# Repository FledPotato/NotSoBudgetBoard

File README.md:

# NotSoBudgetBoard
First keyboard design, which definitely won't save myself or anyone else money.

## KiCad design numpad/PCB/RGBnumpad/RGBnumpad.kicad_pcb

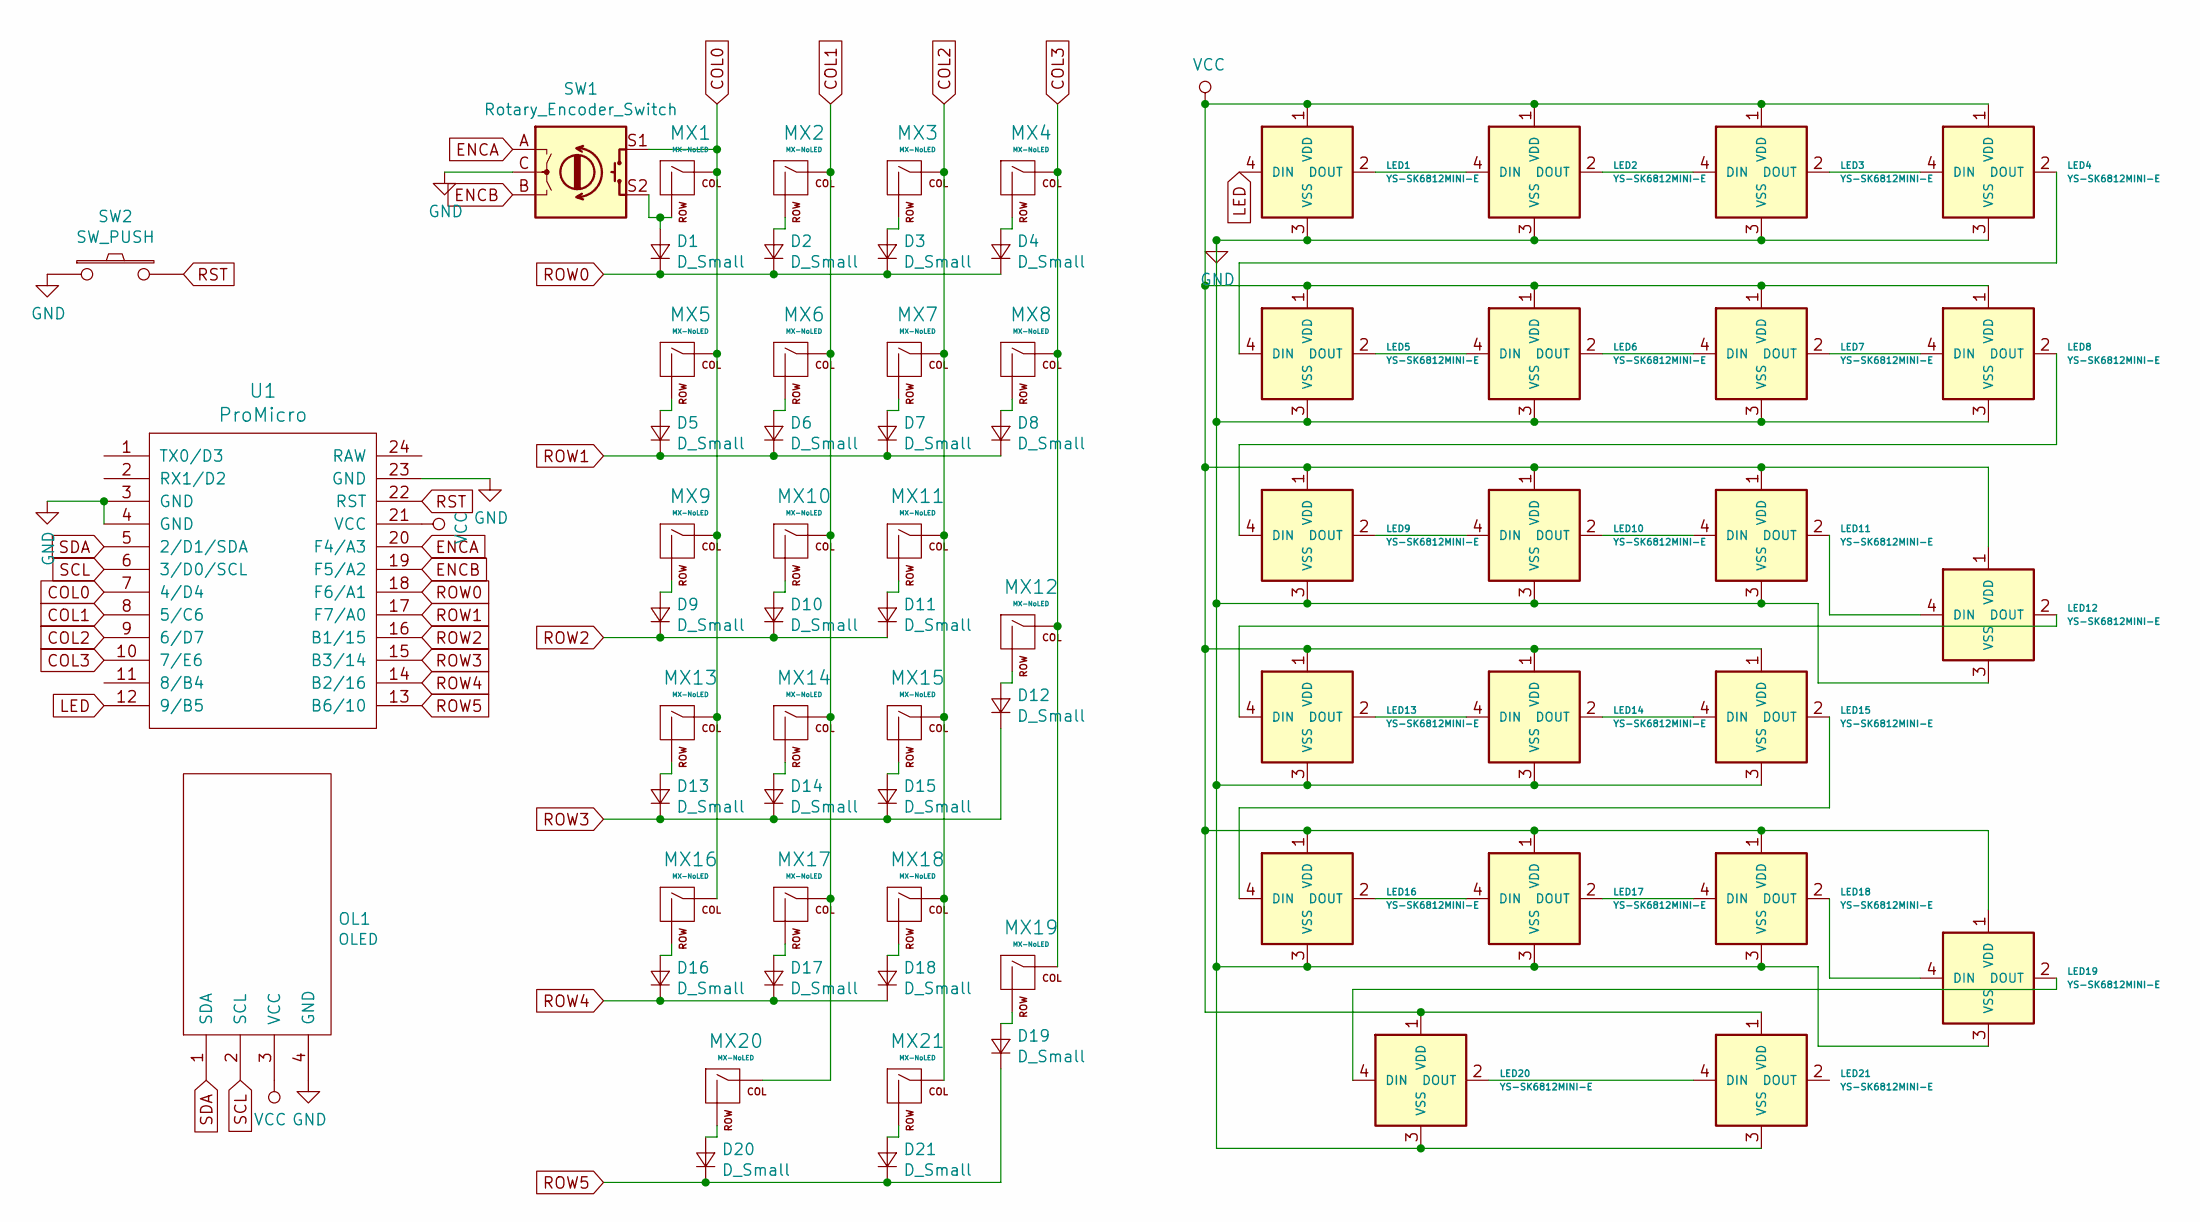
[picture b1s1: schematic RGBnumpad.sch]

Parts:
D1, D2, D3, D4, D5, D6, D7, D8, D9, D10, D11, D12, D13, D14, D15, D16, D17, D18, D19, D20, D21: D_Small; D_DO-35_SOD27_P7.62mm_Horizontal
LED1, LED2, LED3, LED4, LED5, LED6, LED7, LED8, LED9, LED10, LED11, LED12, LED13, LED14, LED15, LED16, LED17, LED18, LED19, LED20, LED21: YS-SK6812MINI-E
MX1, MX2, MX3, MX4, MX5, MX6, MX7, MX8, MX9, MX10, MX11, MX13, MX14, MX15, MX16, MX17, MX18, MX21: MX-NoLED; MXOnly-1U-NoLED
MX12, MX19, MX20: MX-NoLED; MXOnly-2U-ReversedStabilizers-NoLED
OL1: OLED; OLED_v2
SW1: Rotary_Encoder_Switch; RotaryEncoder_Alps_EC11E-Switch_Vertical_H20mm
SW2: SW_PUSH; ResetSW
U1: ProMicro; ProMicro_v3

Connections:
COL0: MX1.1 (COL), MX5.1 (COL), MX9.1 (COL), MX13.1 (COL), MX16.1 (COL), SW1.S1, U1.7 (4/D4)
COL1: MX2.1 (COL), MX6.1 (COL), MX10.1 (COL), MX14.1 (COL), MX17.1 (COL), MX20.1 (COL), U1.8 (5/C6)
COL2: MX3.1 (COL), MX7.1 (COL), MX11.1 (COL), MX15.1 (COL), MX18.1 (COL), MX21.1 (COL), U1.9 (6/D7)
COL3: MX4.1 (COL), MX8.1 (COL), MX12.1 (COL), MX19.1 (COL), U1.10 (7/E6)
ENCA: SW1.A, U1.20 (F4/A3)
ENCB: SW1.B, U1.19 (F5/A2)
GND: LED1.3 (VSS), LED2.3 (VSS), LED3.3 (VSS), LED4.3 (VSS), LED5.3 (VSS), LED6.3 (VSS), LED7.3 (VSS), LED8.3 (VSS), LED9.3 (VSS), LED10.3 (VSS), LED11.3 (VSS), LED12.3 (VSS), LED13.3 (VSS), LED14.3 (VSS), LED15.3 (VSS), LED16.3 (VSS), LED17.3 (VSS), LED18.3 (VSS), LED19.3 (VSS), LED20.3 (VSS), LED21.3 (VSS), OL1.4 (GND), SW1.C, SW2.1, U1.3 (GND), U1.4 (GND), U1.23 (GND)
LED: LED1.4 (DIN), U1.12 (9/B5)
unnamed: D1.2 (A), MX1.2 (ROW), SW1.S2
unnamed: D2.2 (A), MX2.2 (ROW)
unnamed: D3.2 (A), MX3.2 (ROW)
unnamed: D4.2 (A), MX4.2 (ROW)
unnamed: D5.2 (A), MX5.2 (ROW)
unnamed: D6.2 (A), MX6.2 (ROW)
unnamed: D7.2 (A), MX7.2 (ROW)
unnamed: D8.2 (A), MX8.2 (ROW)
unnamed: D9.2 (A), MX9.2 (ROW)
unnamed: D10.2 (A), MX10.2 (ROW)
unnamed: D11.2 (A), MX11.2 (ROW)
unnamed: D12.2 (A), MX12.2 (ROW)
unnamed: D13.2 (A), MX13.2 (ROW)
unnamed: D14.2 (A), MX14.2 (ROW)
unnamed: D15.2 (A), MX15.2 (ROW)
unnamed: D16.2 (A), MX16.2 (ROW)
unnamed: D17.2 (A), MX17.2 (ROW)
unnamed: D18.2 (A), MX18.2 (ROW)
unnamed: D19.2 (A), MX19.2 (ROW)
unnamed: D20.2 (A), MX20.2 (ROW)
unnamed: D21.2 (A), MX21.2 (ROW)
unnamed: LED1.2 (DOUT), LED2.4 (DIN)
unnamed: LED2.2 (DOUT), LED3.4 (DIN)
unnamed: LED3.2 (DOUT), LED4.4 (DIN)
unnamed: LED4.2 (DOUT), LED5.4 (DIN)
unnamed: LED5.2 (DOUT), LED6.4 (DIN)
unnamed: LED6.2 (DOUT), LED7.4 (DIN)
unnamed: LED7.2 (DOUT), LED8.4 (DIN)
unnamed: LED8.2 (DOUT), LED9.4 (DIN)
unnamed: LED10.2 (DOUT), LED11.4 (DIN)
unnamed: LED9.2 (DOUT), LED10.4 (DIN)
unnamed: LED11.2 (DOUT), LED12.4 (DIN)
unnamed: LED12.2 (DOUT), LED13.4 (DIN)
unnamed: LED13.2 (DOUT), LED14.4 (DIN)
unnamed: LED14.2 (DOUT), LED15.4 (DIN)
unnamed: LED15.2 (DOUT), LED16.4 (DIN)
unnamed: LED16.2 (DOUT), LED17.4 (DIN)
unnamed: LED17.2 (DOUT), LED18.4 (DIN)
unnamed: LED18.2 (DOUT), LED19.4 (DIN)
unnamed: LED19.2 (DOUT), LED20.4 (DIN)
unnamed: LED20.2 (DOUT), LED21.4 (DIN)
ROW0: D1.1 (K), D2.1 (K), D3.1 (K), D4.1 (K), U1.18 (F6/A1)
ROW1: D5.1 (K), D6.1 (K), D7.1 (K), D8.1 (K), U1.17 (F7/A0)
ROW2: D9.1 (K), D10.1 (K), D11.1 (K), U1.16 (B1/15)
ROW3: D12.1 (K), D13.1 (K), D14.1 (K), D15.1 (K), U1.15 (B3/14)
ROW4: D16.1 (K), D17.1 (K), D18.1 (K), U1.14 (B2/16)
ROW5: D19.1 (K), D20.1 (K), D21.1 (K), U1.13 (B6/10)
RST: SW2.2, U1.22 (RST)
SCL: OL1.2 (SCL), U1.6 (3/D0/SCL)
SDA: OL1.1 (SDA), U1.5 (2/D1/SDA)
VCC: LED1.1 (VDD), LED2.1 (VDD), LED3.1 (VDD), LED4.1 (VDD), LED5.1 (VDD), LED6.1 (VDD), LED7.1 (VDD), LED8.1 (VDD), LED9.1 (VDD), LED10.1 (VDD), LED11.1 (VDD), LED12.1 (VDD), LED13.1 (VDD), LED14.1 (VDD), LED15.1 (VDD), LED16.1 (VDD), LED17.1 (VDD), LED18.1 (VDD), LED19.1 (VDD), LED20.1 (VDD), LED21.1 (VDD), OL1.3 (VCC), U1.21 (VCC)

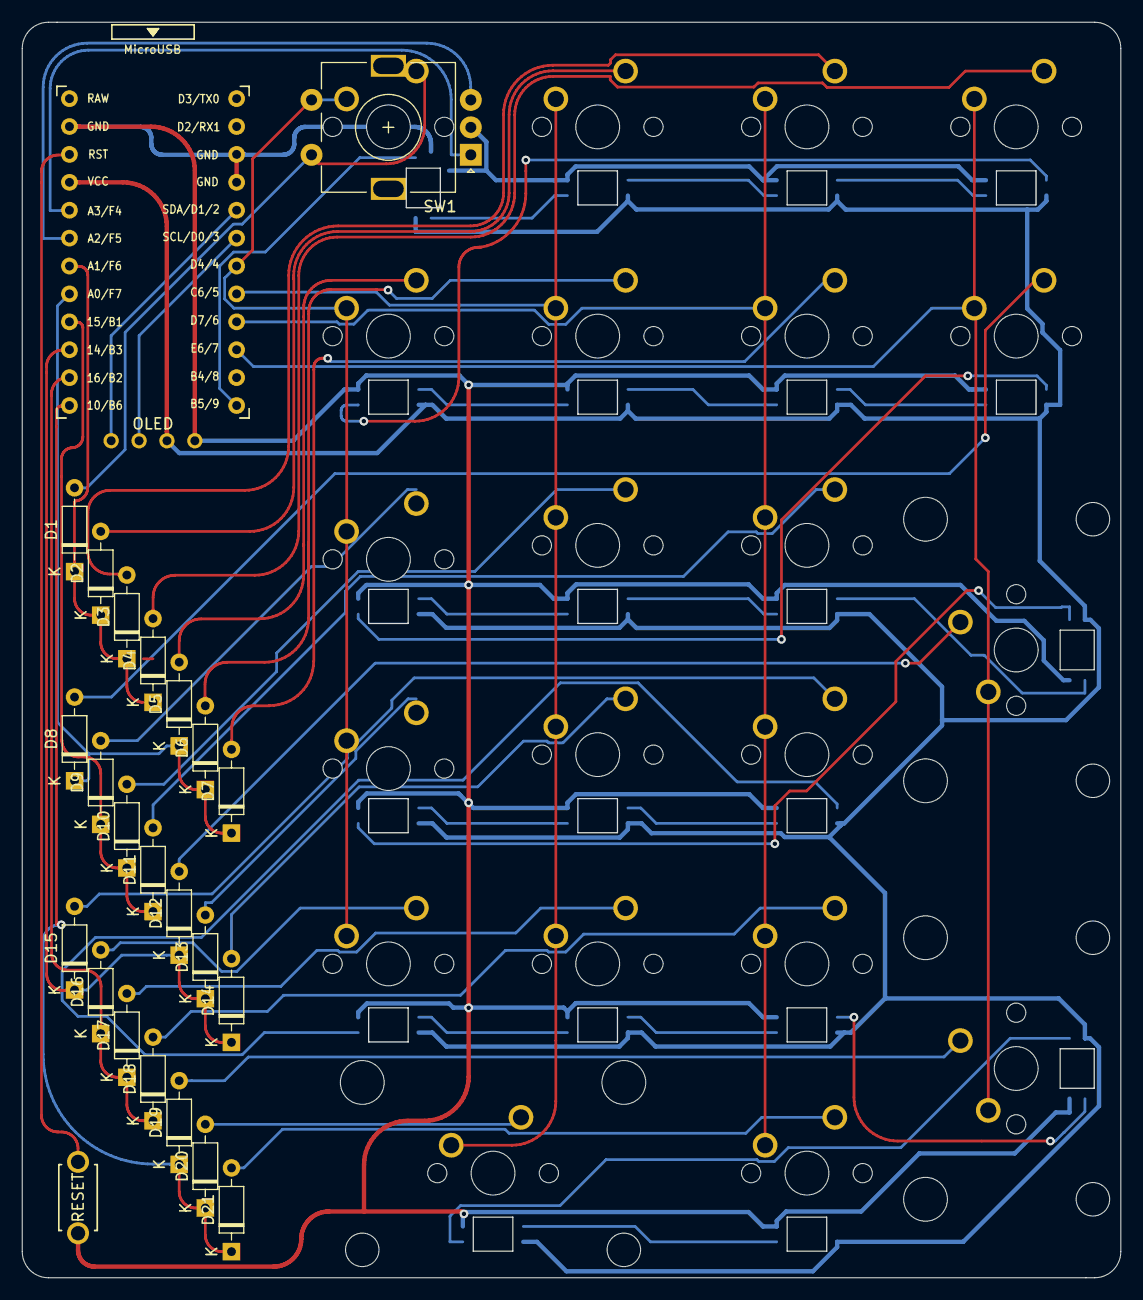
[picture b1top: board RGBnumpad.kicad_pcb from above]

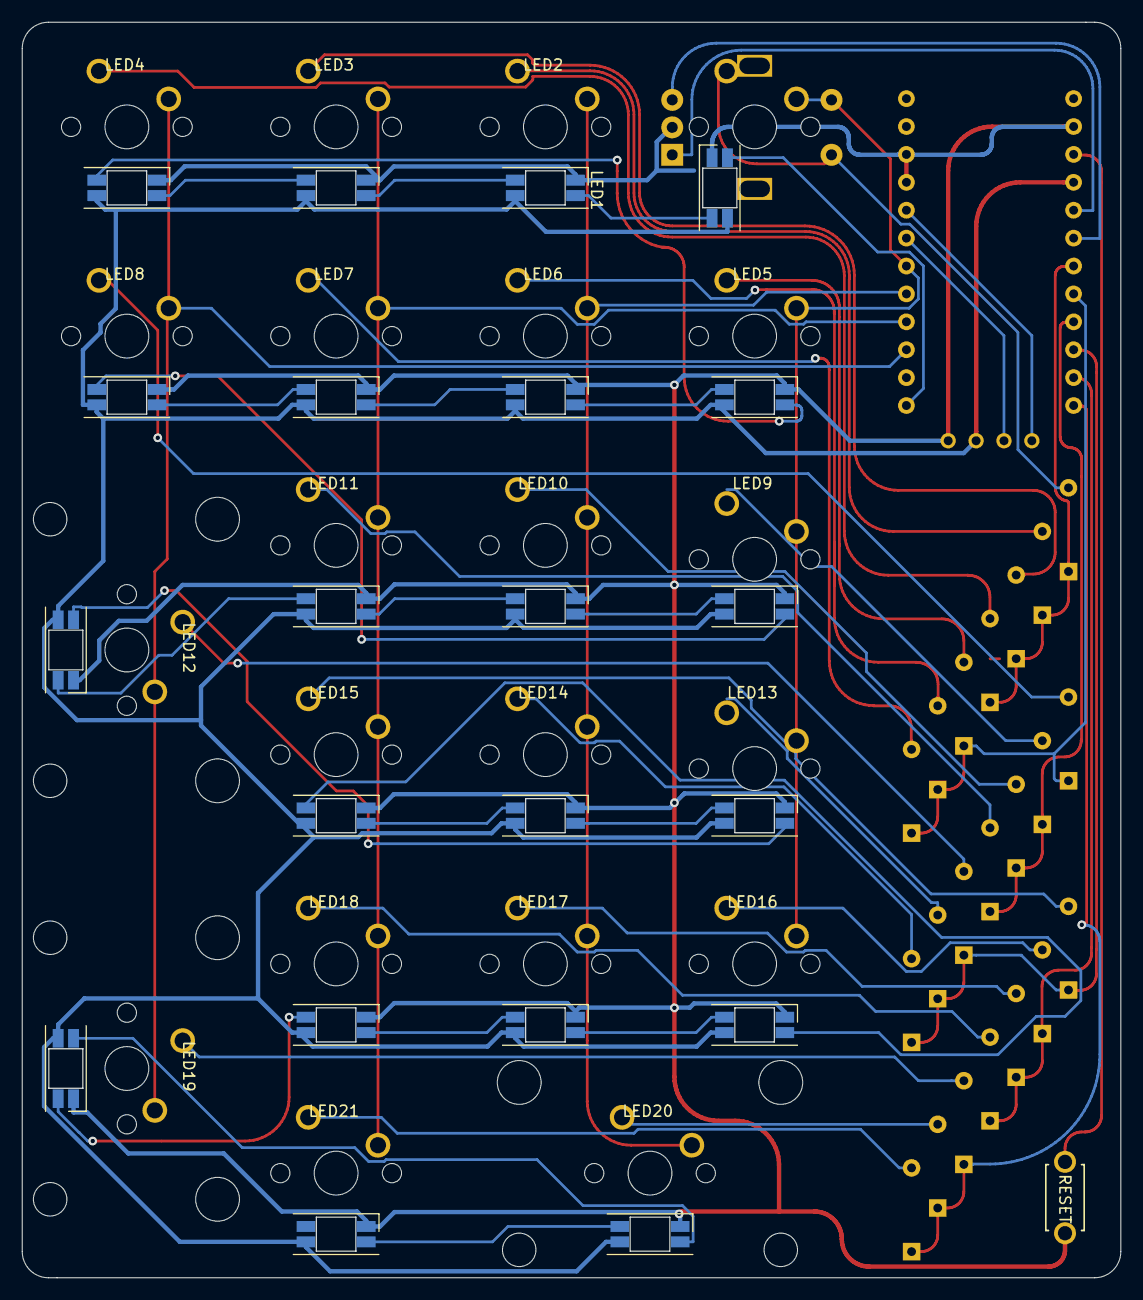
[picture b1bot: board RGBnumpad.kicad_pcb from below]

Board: 2 copper layers, 99.9 x 114.2 mm, 67 parts (21 on the bottom side), 59 nets.

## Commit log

2021-02-11 Add submodules
2021-02-12 Beginning progress, getting there with the schematic
    Also got better submodules or whatever they are
2021-02-13 Learned what a fucking global label is
    Why the hell did i not know what that does i thought it just looked cool
2021-02-16 Pretty much made the entire thing this commit
    Auto routed kek
2021-03-05 routing
    curvyyyy
